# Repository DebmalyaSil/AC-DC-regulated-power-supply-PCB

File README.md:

# AC-DC-regulated-power-supply-PCB

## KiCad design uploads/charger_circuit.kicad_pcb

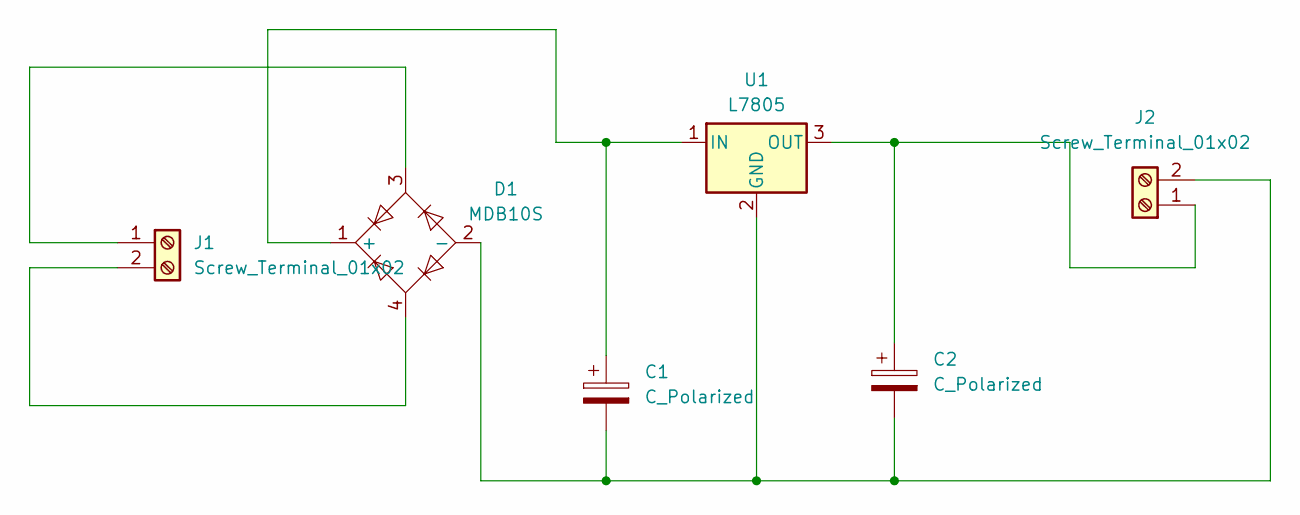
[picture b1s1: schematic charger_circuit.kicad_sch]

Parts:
C1, C2: C_Polarized; CP_Radial_D6.3mm_P2.50mm
D1: MDB10S; TSSOP-4_4.4x5mm_P4mm
J1, J2: Screw_Terminal_01x02; TerminalBlock_Phoenix_MKDS-1,5-2_1x02_P5.00mm_Horizontal
U1: L7805; TO-220-3_Vertical

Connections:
unnamed: C1.1, D1.1 (+), U1.1 (IN)
unnamed: C1.2, C2.2, D1.2 (-), J2.2, U1.2 (GND)
unnamed: D1.3, J1.1
unnamed: D1.4, J1.2
unnamed: C2.1, J2.1, U1.3 (OUT)

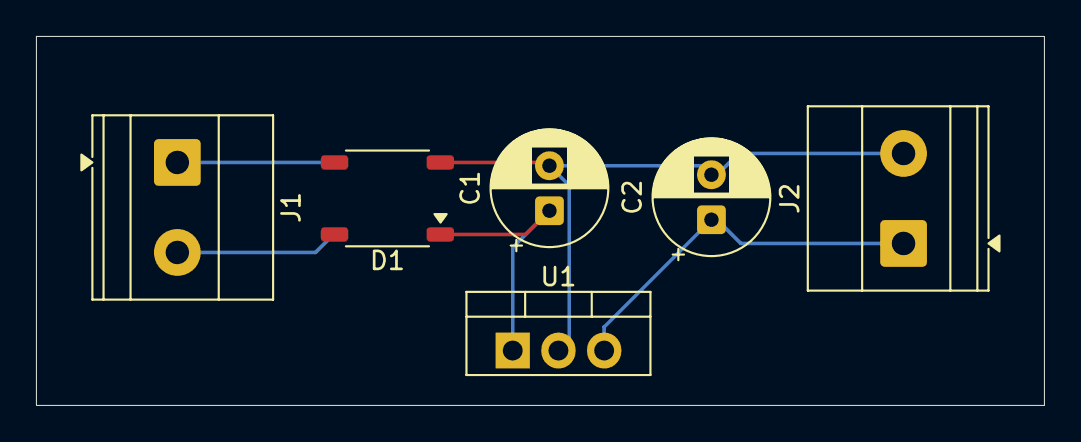
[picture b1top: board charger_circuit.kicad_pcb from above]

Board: 2 copper layers, 56.0 x 20.5 mm, 6 parts (0 on the bottom side), 5 nets.

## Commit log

2025-11-23 Create resources
2025-11-23 Create a
2025-11-23 circuit upload
2025-11-23 Create gerber
2025-11-23 Create empty
